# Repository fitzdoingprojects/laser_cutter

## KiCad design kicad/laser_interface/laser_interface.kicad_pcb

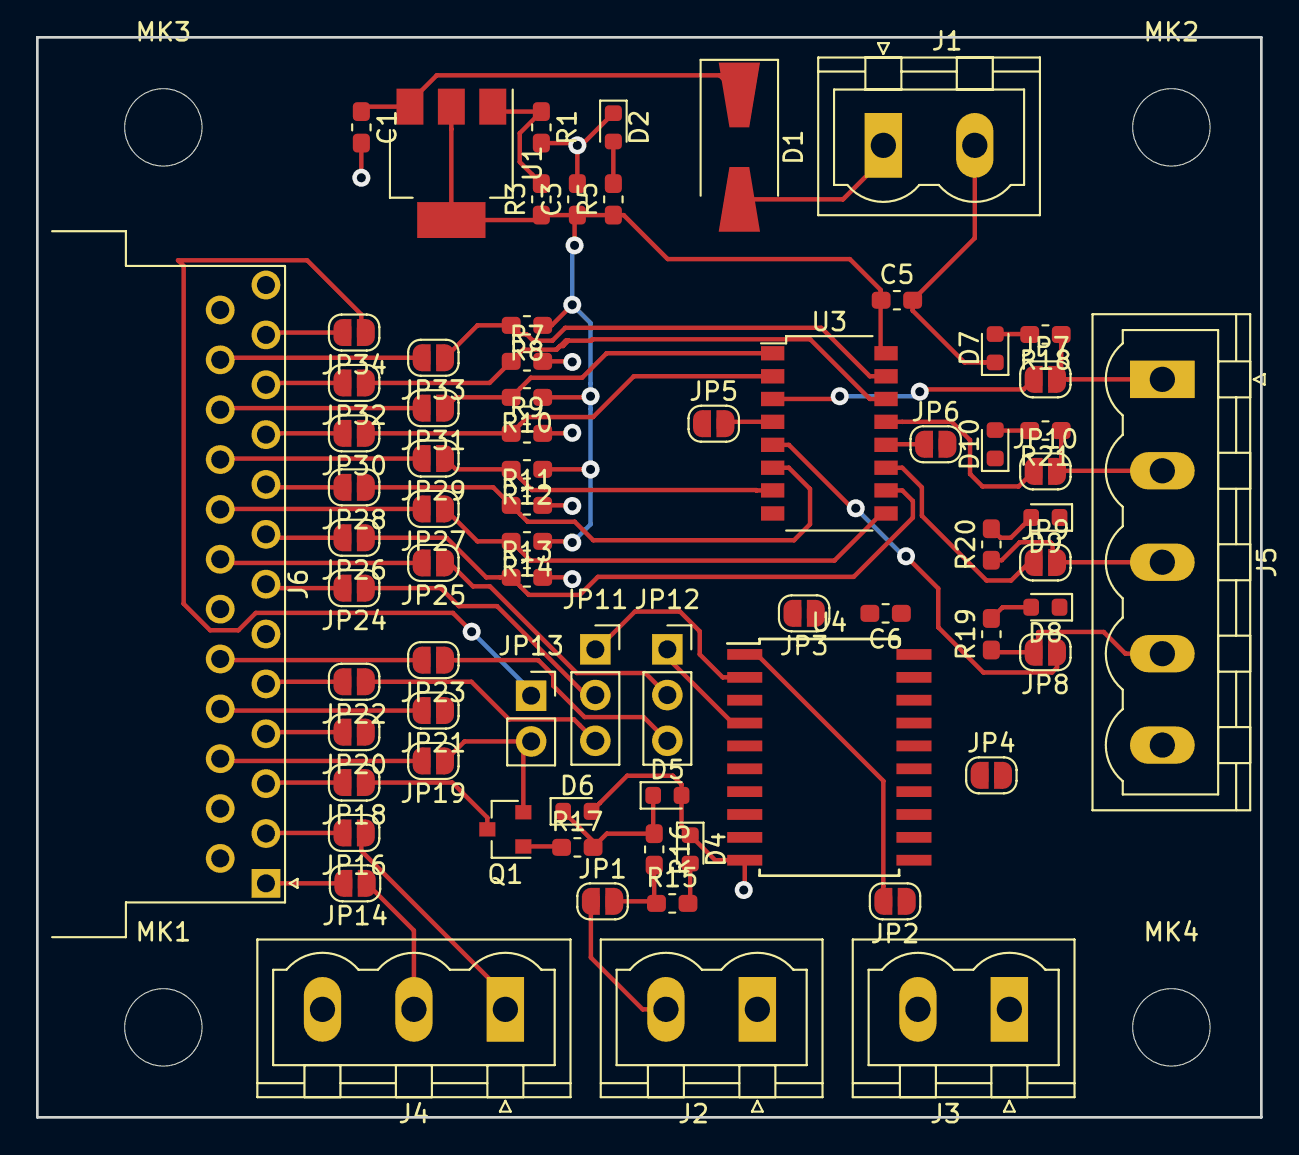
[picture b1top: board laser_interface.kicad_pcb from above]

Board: 2 copper layers, 68.0 x 60.0 mm, 77 parts (0 on the bottom side), 67 nets.

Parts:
C1, C3: C_Small; C_0603_1608Metric_Pad1.05x0.95mm_HandSolder
C5, C6: 0.1uF; C_0603_1608Metric_Pad1.05x0.95mm_HandSolder
D1: D_Schottky_Small; D_SMA-SMB_Universal_Handsoldering
D2, D4: GREEN; D_0603_1608Metric_Pad0.88x0.95mm_HandSolder
D5: 5.1V Zener; D_0603_1608Metric_Pad0.88x0.95mm_HandSolder
D6: D_Small; D_0603_1608Metric_Pad0.88x0.95mm_HandSolder
D7, D8, D9, D10: RED; D_0603_1608Metric_Pad0.88x0.95mm_HandSolder
J1: 12V; PhoenixContact_MSTBVA_2,5_2-G-5,08_1x02_P5.08mm_Vertical
J2: ENABLE; PhoenixContact_MSTBVA_2,5_2-G-5,08_1x02_P5.08mm_Vertical
J3: MODULATE; PhoenixContact_MSTBVA_2,5_2-G-5,08_1x02_P5.08mm_Vertical
J4: ANALOG; PhoenixContact_MSTBVA_2,5_3-G-5,08_1x03_P5.08mm_Vertical
J5: Conn_01x05; PhoenixContact_MSTBVA_2,5_5-G-5,08_1x05_P5.08mm_Vertical
J6: DB25_Female; DSUB-25_Female_Horizontal_P2.77x2.54mm_EdgePinOffset9.40mm
JP1, JP2, JP3, JP4, JP5, JP6, JP7, JP8, JP9, JP10, JP14, JP16, JP18, JP19, JP20, JP21, JP22, JP23, JP24, JP25, JP26, JP27, JP28, JP29, JP30, JP31, JP32, JP33, JP34: Jumper_NO_Small; SolderJumper-2_P1.3mm_Open_RoundedPad1.0x1.5mm
JP11, JP12: Jumper_3_Open; PinSocket_1x03_P2.54mm_Vertical
JP13: Jumper_NO_Small; PinSocket_1x02_P2.54mm_Vertical
MK1, MK2, MK3, MK4: M4; MountingHole_4.3mm_M4
Q1: MMBT3904; SOT-23
R1, R3: R_Small; R_0603_1608Metric_Pad1.05x0.95mm_HandSolder
R5, R15, R18, R19, R20, R21: 10K; R_0603_1608Metric_Pad1.05x0.95mm_HandSolder
R7, R8, R9, R10, R11, R12, R13, R14: 2.7K; R_0603_1608Metric_Pad1.05x0.95mm_HandSolder
R16, R17: 1K; R_0603_1608Metric_Pad1.05x0.95mm_HandSolder
U1: LM1117-ADJ; SOT-223-3_TabPin2
U3: sn75173; SOP-16_4.4x10.4mm_P1.27mm
U4: sn75172; SOIC-20W_7.5x12.8mm_P1.27mm

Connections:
+5V: C3.1, C5.1, C6.1, JP3.1, JP5.1, R3.1, R5.1, R8.1, R10.1, R12.1, R14.1, U1.2, U3.16, U4.20
/ANALOG_FWD: J4.2, JP14.1
/ANALOG_REFL: J4.1, JP16.1
/DIGITAL_FWD: J5.4, JP8.2, R19.1
/DIGITAL_FWD+: JP28.1, R11.1, U3.6
/DIGITAL_FWD-: JP29.1, R12.2, U3.7
/DIGITAL_REFL: J5.3, JP9.2, R20.1
/DIGITAL_REFL+: JP26.1, R13.1, U3.10
/DIGITAL_REFL-: JP27.1, R14.2, U3.9
/DUTY_CYCLE: J5.1, JP7.2, R18.1
/DUTY_CYCLE+: JP30.1, R9.1, U3.2
/DUTY_CYCLE-: JP31.1, R10.2, U3.1
/ENABLE: JP18.1, Q1.3
/LASER_ENABLE: J2.2, JP1.1
/LASER_MOD: J3.2, JP2.1
/MOD+: JP11.2, JP24.1
/MOD-: JP12.2, JP25.1
/RETURN: JP13.2, JP19.1, Q1.2
/TEST_ENABLE: JP13.1, JP34.1
/TEST_MOD+: JP11.3, JP22.1
/TEST_MOD-: JP12.3, JP23.1
/VSWR: J5.2, JP10.2, R21.1
/VSWR+: JP32.1, R7.1, U3.14
/VSWR-: JP33.1, R8.2, U3.15
GND: C1.2, C3.2, C5.2, C6.2, D2.1, D4.1, D5.2, D6.2, D7.1, D8.1, D9.1, D10.1, J1.2, J2.1, J3.1, J4.3, J5.5, JP4.2, JP6.2, R1.2, R7.2, R9.2, R11.2, R13.2, U3.8, U4.10
unnamed: C1.1, D1.1, U1.3
unnamed: D1.2, J1.1
unnamed: D2.2, R5.2
unnamed: D4.2, R15.2
unnamed: D5.1, D6.1, R16.1, R17.2
unnamed: D7.2, R18.2
unnamed: D8.2, R19.2
unnamed: D9.2, R20.2
unnamed: D10.2, R21.2
unnamed: J6.1, JP14.2
unnamed: J6.2, JP16.2
unnamed: J6.3, JP18.2
unnamed: J6.4, JP20.2
unnamed: J6.5, JP22.2
unnamed: J6.7, JP24.2
unnamed: J6.8, JP26.2
unnamed: J6.9, JP28.2
unnamed: J6.10, JP30.2
unnamed: J6.11, JP32.2
unnamed: J6.12, JP34.2
unnamed: J6.16, JP19.2
unnamed: J6.17, JP21.2
unnamed: J6.18, JP23.2
unnamed: J6.20, JP25.2
unnamed: J6.21, JP27.2
unnamed: J6.22, JP29.2
unnamed: J6.23, JP31.2
unnamed: J6.24, JP33.2
unnamed: JP1.2, R15.1, R16.2
unnamed: JP2.2, U4.1
unnamed: JP3.2, U4.5
unnamed: JP4.1, U4.15
unnamed: JP5.2, U3.4
unnamed: JP6.1, U3.12
unnamed: JP7.1, U3.3
unnamed: JP8.1, U3.5
unnamed: JP9.1, U3.11
unnamed: JP10.1, U3.13
unnamed: JP11.1, U4.2
unnamed: JP12.1, U4.4
unnamed: Q1.1, R17.1
unnamed: R1.1, R3.2, U1.1

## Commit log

2018-10-13 add full board for laser interface
